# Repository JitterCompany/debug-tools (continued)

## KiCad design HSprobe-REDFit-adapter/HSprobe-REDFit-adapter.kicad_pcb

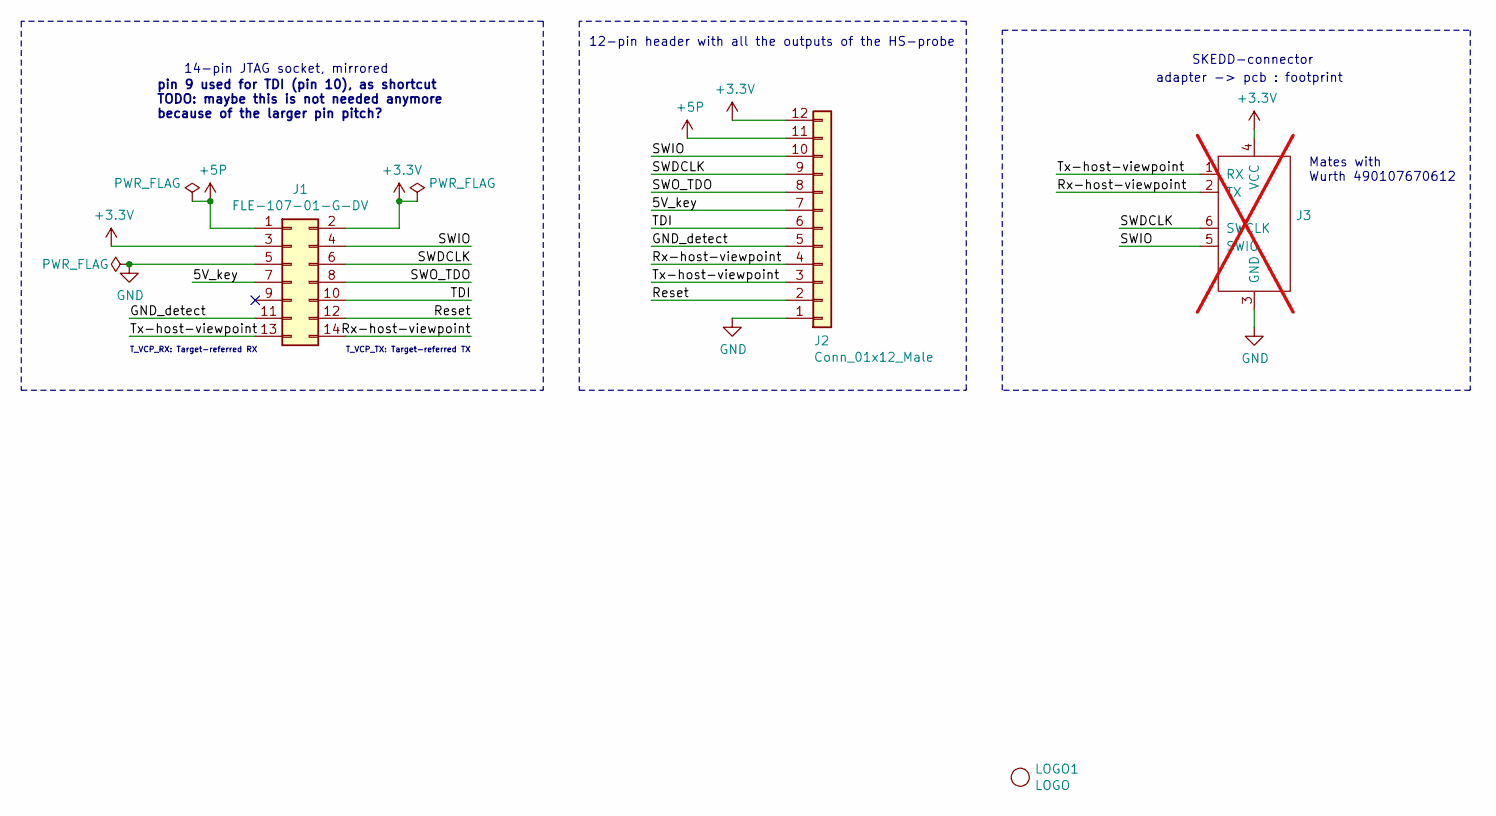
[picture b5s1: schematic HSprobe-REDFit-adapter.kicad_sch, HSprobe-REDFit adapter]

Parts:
J1: FLE-107-01-G-DV; PinSocket_2x07_P1.27mm_Vertical_SMD; MPN FLE-107-01-G-DV
J2: Conn_01x12_Male; PinHeader_2x06_P2.54mm_Vertical
J3: DNI; WR-WST_REDFIT-6-pins_490107670612-adapter_to_pcb; not fitted
LOGO1: LOGO; Jitter-mini

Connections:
+3.3V: J1.2, J1.3, J2.12, J3.4 (VCC)
+5P: J1.1, J2.11
/5V_key: J1.7, J2.7
/GND_detect: J1.11, J2.5
/Reset: J1.12, J2.2
/Rx-host-viewpoint: J1.14, J2.4, J3.2 (TX)
/SWDCLK: J1.6, J2.9, J3.6 (SWCLK)
/SWIO: J1.4, J2.10, J3.5 (SWIO)
/SWO_TDO: J1.8, J2.8
/TDI: J1.10, J2.6
/Tx-host-viewpoint: J1.13, J2.3, J3.1 (RX)
GND: J1.5, J2.1, J3.3 (GND)

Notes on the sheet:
pin 9 used for TDI (pin 10), as shortcut TODO: maybe this is not needed anymore because of the larger pin pitch?
Mates with Wurth 490107670612
T_VCP_RX: Target-referred RX
adapter -> pcb : footprint
T_VCP_TX: Target-referred TX
14-pin JTAG socket, mirrored
12-pin header with all the outputs of the HS-probe
SKEDD-connector

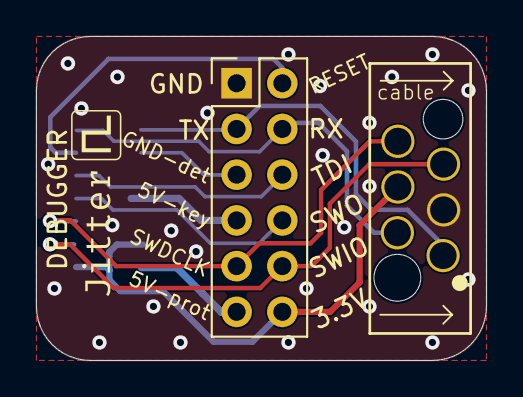
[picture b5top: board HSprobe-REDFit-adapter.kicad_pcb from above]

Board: 2 copper layers, 25.0 x 18.0 mm, 4 parts (1 on the bottom side), 12 nets.

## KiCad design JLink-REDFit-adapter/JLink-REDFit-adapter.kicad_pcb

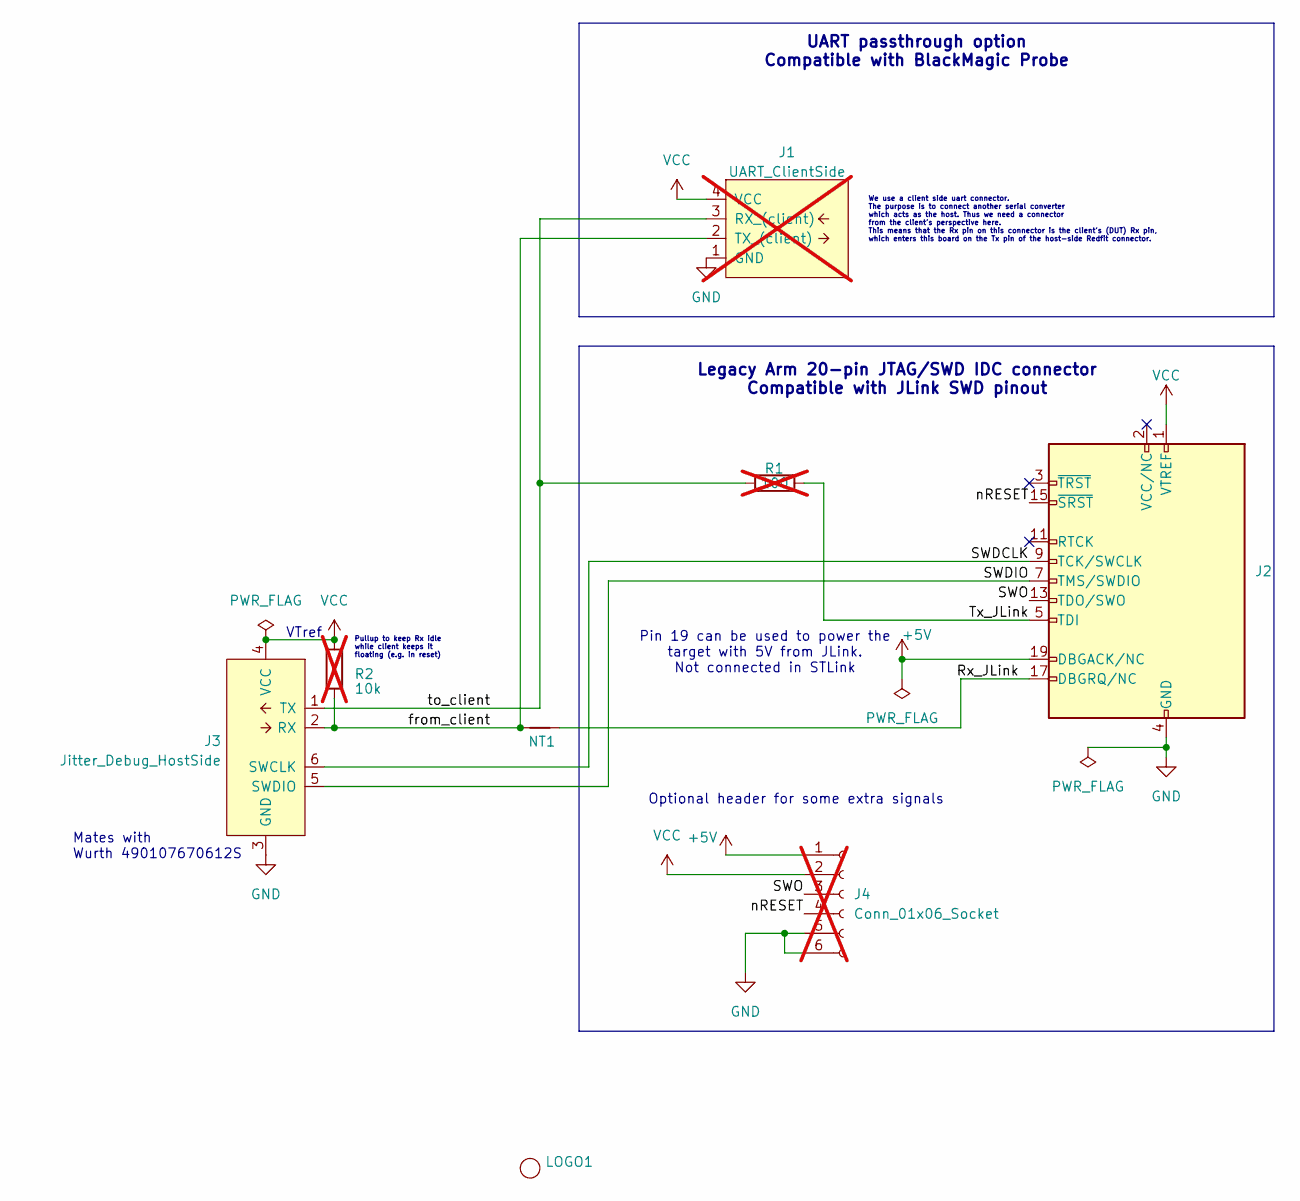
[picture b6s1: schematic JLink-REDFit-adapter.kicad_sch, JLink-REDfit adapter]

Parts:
J1: UART_ClientSide; Molex_PicoBlade_53261-0471_1x04-1MP_P1.25mm_Horizontal; not fitted
J2: 2x10 female header 2.54mm pitch. With a notch/key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; JLink_PinHeader_2x10_2.54_Horizontal
J3: Jitter_Debug_HostSide; WR-WST_REDFIT-6-pins_490107670612-adapter_to_pcb
J4: Conn_01x06_Socket; PinHeader_1x06_P2.54mm_Vertical; not fitted
LOGO1: LOGO; JitterLogo
NT1: NetTie_2; NetTie-2_SMD_Pad0.2mm
R1: 100; R_0603_1608Metric; not fitted
R2: 10k; R_0603_1608Metric; not fitted

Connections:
+5V: J2.19 (DBGACK/NC), J4.1
/Rx_JLink: J2.17 (DBGRQ/NC), NT1.2
/SWDCLK: J2.9 (TCK/SWCLK), J3.6 (SWCLK)
/SWDIO: J2.7 (TMS/SWDIO), J3.5 (SWDIO)
/SWO: J2.13 (TDO/SWO), J4.3
/Tx_JLink: J2.5 (TDI), R1.1
/from_client: J1.2 (TX_(client)), J3.2 (RX), NT1.1, R2.2
/nRESET: J2.15 (~SRST), J4.4
/to_client: J1.3 (RX_(client)), J3.1 (TX), R1.2
GND: J1.1 (GND), J2.4 (GND), J2.6 (GND), J2.8 (GND), J2.10 (GND), J2.12 (GND), J2.14 (GND), J2.16 (GND), J2.18 (GND), J2.20 (GND), J3.3 (GND), J4.5, J4.6
VCC: J1.4 (VCC), J2.1 (VTREF), J3.4 (VCC), J4.2, R2.1

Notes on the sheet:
Pin 19 can be used to power the target with 5V from JLink. Not connected in STLink
UART passthrough option Compatible with BlackMagic Probe
VTref
Mates with Wurth 490107670612S
We use a client side uart connector. The purpose is to connect another serial converter which acts as the host. Thus we need a connector from the client's perspective here. This means that the Rx pin on this connector is the client's (DUT) Rx pin, which enters this board on the Tx pin of the host-s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
Optional header for some extra signals
Pullup to keep Rx idle while client keeps it floating (e.g. in reset)
Legacy Arm 20-pin JTAG/SWD IDC connector Compatible with JLink SWD pinout

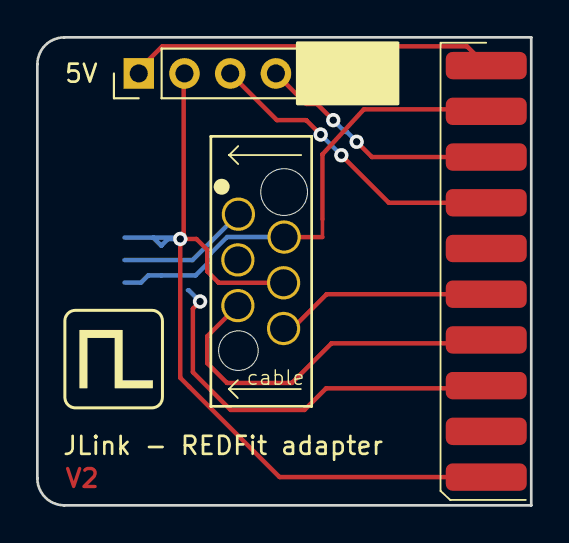
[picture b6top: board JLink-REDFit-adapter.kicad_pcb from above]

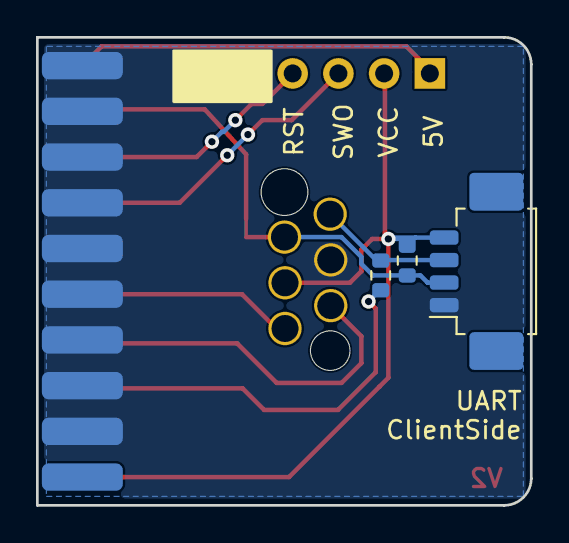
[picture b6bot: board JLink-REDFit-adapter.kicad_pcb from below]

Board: 2 copper layers, 27.4 x 26.0 mm, 8 parts (3 on the bottom side), 11 nets.

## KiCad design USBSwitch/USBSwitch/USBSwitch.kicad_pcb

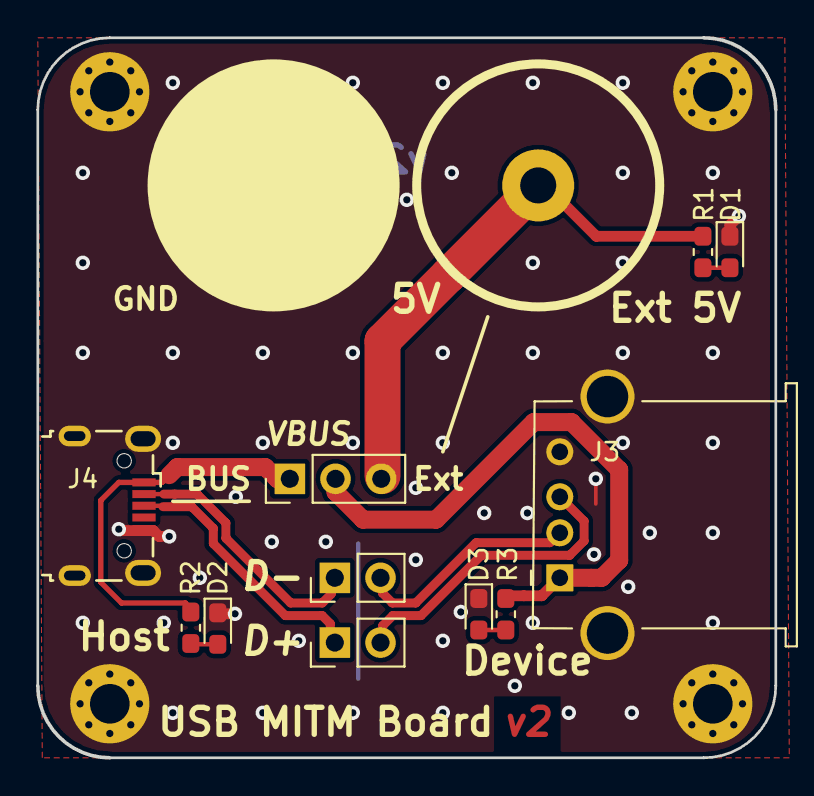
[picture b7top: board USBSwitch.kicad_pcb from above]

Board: 2 copper layers, 41.0 x 40.0 mm, 17 parts (0 on the bottom side), 11 nets.

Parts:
D1, D2, D3: LED; LED_0603_1608Metric_Pad1.05x0.95mm_HandSolder
H1, H2, H3, H4: MountingHole_Pad; MountingHole_2.2mm_M2_Pad_Via
J1, J2: Conn_01x01_Female; CT3149_Banana_Jack_4mm
J3: USB_A; USB_A_Wuerth_61400416021_Horizontal
J4: USB_B_Micro; USB_Micro-B_Wuerth_629105150521
JP1: Jumper_NC_Dual; PinHeader_1x03_P2.54mm_Vertical
JP2, JP3: Jumper; PinHeader_1x02_P2.54mm_Vertical
R1, R2, R3: 220; R_0603_1608Metric_Pad1.05x0.95mm_HandSolder

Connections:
+5V: J1.1, JP1.3, R1.1
/DEVICE_D+: J3.3, JP2.2
/DEVICE_D-: J3.2, JP3.2
/HOST_D+: J4.3, JP2.1
/HOST_D-: J4.2, JP3.1
GND: D1.1, D2.1, D3.1, H1.1, H2.1, H3.1, H4.1, J2.1, J3.4, J3.5, J4.5, J4.6
unnamed: D1.2, R1.2
unnamed: D2.2, R2.2
unnamed: D3.2, R3.2
VBUS: J4.1, JP1.1, R2.1
VCC: J3.1, JP1.2, R3.1

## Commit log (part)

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2018-12-19 Add jtag to swd converter board
    This PCB converts a 10 pin jtag connector to 4 pin 2.54 pitch header.
2018-12-20 Change ground plane
2018-12-20 Update Gerber files
2018-12-20 Add fabrication output dir setting
2019-03-07 Add USB MITM board and update jtag-swd adapter
2019-03-07 Fix usb switch top pour
2019-03-07 Update output dir
2020-02-05 Update USBSwitch
2020-02-05 USBSwitch ( =MITM board ): release V2
2020-02-10 USBSwitch (=Mitm board): final production BOM (V2)
2021-03-11 Add SKEDD to uart+swd board
    This is an adapter board that connects between the board-under-test with the
    Wurth SKEDD connector and provides SWD + UART (e.g. via BlackMagic
    Probe).
2021-12-17 Add HS-probe converter board
    Use the probe-rs/hs-probe with SKEDD connector
2021-12-17 SKED-jtag+uart, jtag-swd: add MPN info, BOM
2022-07-21 Add Readme
2022-07-27 Add JLink redfit adapter board
2023-03-24 Breakout JLink: rotate SKEDD footprint with correct cable orientation
    (the previous version works OK but the silkscreen arrows point the wrong way)
2023-03-29 Breakout for JLink to Tag Connect TC2030-IDC (microchip)
    Note: the TC2030-IDC is generic, but this converter is
    microchip-specific. NOT SWD/JTAG compatible!
2023-08-03 Breakout JLink: release V2
    - inline UART tx resistor to handle conflict if JLink + Blackmagic hosts both connected
    - UART rx pullup resistor to avoid noise if target disconnected or in reset
2026-04-20 Update symbols and footprints and rename to BMP
2026-04-20 Remove old files
2026-04-20 Add images
2026-04-21 Add Logos back with schematic symbol. Reverse SWO/RST connector
2026-04-21 Use mini logo
